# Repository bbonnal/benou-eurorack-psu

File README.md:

# Benou Eurorack PSU

A +12V +5V -12V power supply for modular synthesizer application. Based on the LT3083EQ_PBF linear regulator.

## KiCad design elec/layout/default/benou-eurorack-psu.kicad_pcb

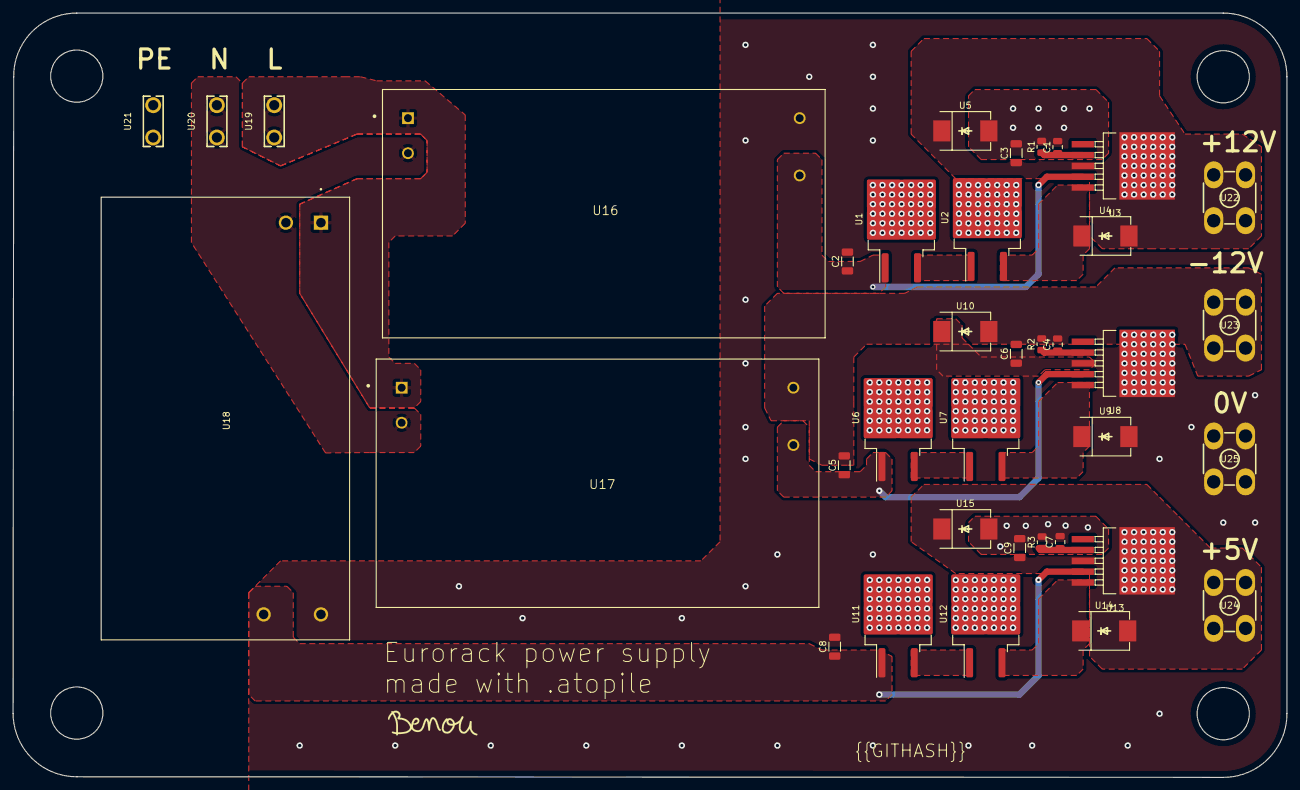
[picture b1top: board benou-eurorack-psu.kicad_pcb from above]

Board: 2 copper layers, 200.0 x 120.0 mm, 38 parts (1 on the bottom side), 18 nets.

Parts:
BenouGraphic: Benou_bot_graphics_15mm
C1, C4, C7: 10.0 pF; C0805
C2, C3, C5, C6, C8, C9: 22uF; C1206
R1, R2: 243k; R0805
R3: 100k; R0805
U1, U2, U6, U7, U11, U12: ?; TO-263-2
U3, U8, U13: DD-PAK-5_L10.2-W8.9-P1.70-LS14.0-BR
U4, U5, U9, U10, U14, U15: SMC_L6.9-W5.9-LS7.9-RD
U16, U17: ?; IRM-30-15
U18: ?; PSK-30D-9
U19, U20, U21: CONN-TH_63849-1
U22, U23, U24, U25: CONN-TH_T34001

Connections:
L: U16.1, U17.1, U18.1, U19.1
N: U16.2, U17.2, U18.2, U20.1
p1: C1.1, R1.1, U3.2
p1-1: C4.1, R2.1, U8.2
p1-2: C7.1, R3.1, U13.2
p2: U1.3, U2.1
p2-1: U2.3, U3.5, U4.1
p2-2: U6.3, U7.1
p2-3: U7.3, U8.5, U9.1
p2-4: U11.3, U12.1
p2-5: U12.3, U13.5, U14.1
v_neg: C1.2, C2.2, C3.2, C6.1, C7.2, C8.2, C9.2, R1.2, R3.2, U5.2, U8.3, U8.6, U9.2, U10.1, U15.2, U16.4, U18.4, U25.1, U25.2, U25.3, U25.4
v_neg-1: C4.2, C5.2, C6.2, R2.2, U10.2, U17.4, U23.1, U23.2, U23.3, U23.4
v_pos: C3.1, U3.3, U3.6, U4.2, U5.1, U22.1, U22.2, U22.3, U22.4
v_pos-1: C9.1, U13.3, U13.6, U14.2, U15.1, U24.1, U24.2, U24.3, U24.4
v_pos-2: C2.1, U1.1, U3.4, U16.3
v_pos-3: C5.1, U6.1, U8.4, U17.3
v_pos-4: C8.1, U11.1, U13.4, U18.3

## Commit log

2023-12-19 Initial commit for benou-eurorack-psu
2023-12-19 init import
2023-12-19 add floatldo module
2023-12-19 add IRM footprint
2023-12-19 add footprints and init board layout
2023-12-19 new fp for ben
2023-12-19 broken error report
2023-12-19 make netlist ready for layout
2023-12-19 move floating LDO to a dedicated module
2023-12-20 finish first rev layout
2023-12-20 improve layout's thermal dissipation
2024-01-03 add missing connection to vneg
2024-01-04 Update .gitlab-ci.yml file
2024-01-19 upgrade prject to ato v0.2.1
2024-02-11 add readme
2024-02-11 update to latest compiler
2024-02-11 upgrade ato version
2024-02-11 add ci
2024-02-11 remove dev container
2024-02-11 remove ci
2024-03-24 Change ato version
2024-03-24 Make compatible with last version with github mods
